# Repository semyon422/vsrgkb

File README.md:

# vsrgkb
 Split mechanical keyboard for rhythm games

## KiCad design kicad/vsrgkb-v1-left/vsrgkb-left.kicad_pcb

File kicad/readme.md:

# hardware issues

## v1

Wrong pin choosen for communication. D1 is recommended.  
Pull-up and pull-down resistors are missing for handedness detection.

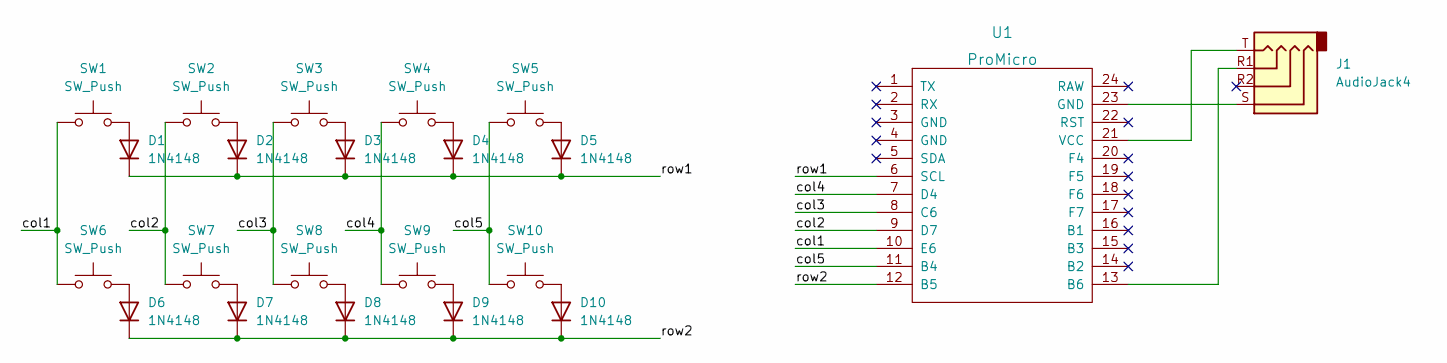
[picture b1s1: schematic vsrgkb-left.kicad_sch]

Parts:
D1, D2, D3, D4, D5, D6, D7, D8, D9, D10: 1N4148; D_DO-35_SOD27_P7.62mm_Horizontal
J1: AudioJack4; Jack_3.5mm_PJ320D_Horizontal
SW1, SW2, SW3, SW4, SW5, SW6, SW7, SW8, SW9, SW10: SW_Push; SW_Hotswap_Kailh_Choc_V1V2_1.00u
U1: ProMicro

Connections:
/col1: SW1.1, SW6.1, U1.10 (E6)
/col2: SW2.1, SW7.1, U1.9 (D7)
/col3: SW3.1, SW8.1, U1.8 (C6)
/col4: SW4.1, SW9.1, U1.7 (D4)
/col5: SW5.1, SW10.1, U1.11 (B4)
/row1: D1.1 (K), D2.1 (K), D3.1 (K), D4.1 (K), D5.1 (K), U1.6 (SCL)
/row2: D6.1 (K), D7.1 (K), D8.1 (K), D9.1 (K), D10.1 (K), U1.12 (B5)
unnamed: D2.2 (A), SW2.2
unnamed: D3.2 (A), SW3.2
unnamed: D6.2 (A), SW6.2
unnamed: D7.2 (A), SW7.2
unnamed: D8.2 (A), SW8.2
unnamed: D9.2 (A), SW9.2
unnamed: D10.2 (A), SW10.2
unnamed: J1.S, U1.23 (GND)
unnamed: D1.2 (A), SW1.2
unnamed: D4.2 (A), SW4.2
unnamed: D5.2 (A), SW5.2
unnamed: J1.R1, U1.13 (B6)
unnamed: J1.T, U1.21 (VCC)

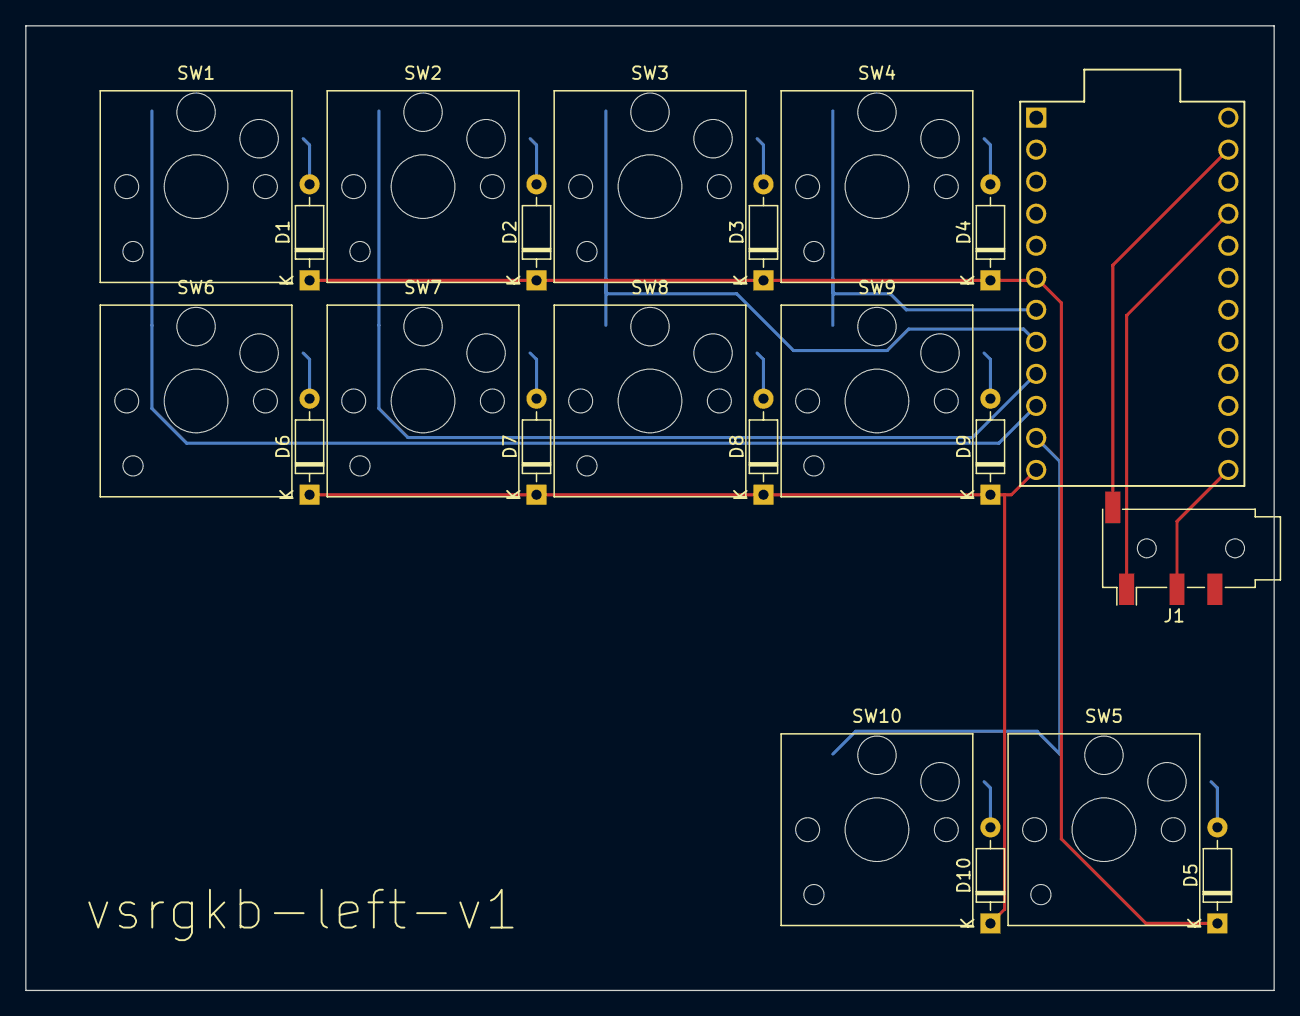
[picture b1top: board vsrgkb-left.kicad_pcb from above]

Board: 2 copper layers, 99.0 x 76.5 mm, 22 parts (0 on the bottom side), 20 nets.

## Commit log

2023-01-23 Add files
2023-03-19 Change SPLIT_HAND_PIN to F4
2023-03-19 Add schs and photos of modified kbd
2023-03-19 Add kbd photos
